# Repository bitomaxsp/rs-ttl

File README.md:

# RS232 to TTL converter

Can be used to connect any 5V logic device to RS232 device such as PC

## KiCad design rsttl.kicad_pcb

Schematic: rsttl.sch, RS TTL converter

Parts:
C1: 0.33uF; C_1210_3225Metric_Pad1.42x2.65mm_HandSolder
C2, C4, C5, C6, C7: 1uF; C_0805_2012Metric_Pad1.15x1.40mm_HandSolder
C3: 0.1uF; C_1210_3225Metric_Pad1.42x2.65mm_HandSolder
D1, D2: LED_Small; LED_0805_2012Metric
J1: DB9_Male; DSUB-9_Male_Horizontal_P2.77x2.84mm_EdgePinOffset9.90mm_Hou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
J2: 7-20V Ext; PinHeader_1x02_P2.54mm_Vertical
J3: TTL Data, 5V; PinHeader_1x06_P2.54mm_Vertical
J5: DB9_Female; DSUB-9_Female_Horizontal_P2.77x2.84mm_EdgePinOffset9.90mm_H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
R1, R2: 1k; R_0805_2012Metric_Pad1.15x1.40mm_HandSolder
U1: NCP1117; SOT-223-3_TabPin2
U2: MAX232; SOP-16_4.55x10.3mm_P1.27mm

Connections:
+5V: C3.1, C4.1, D1.2 (A), D2.2 (A), J3.2, U1.2, U2.16 (VCC)
GND: C1.2, C3.2, C4.2, C6.2, C7.1, J1.5, J2.1, J3.1, J5.5, U1.1, U2.15 (GND)
unnamed: C2.1, U2.1 (C1+)
unnamed: C2.2, U2.3 (C1-)
unnamed: C5.1, U2.4 (C2+)
unnamed: C5.2, U2.5 (C2-)
unnamed: C6.1, U2.2 (VS+)
unnamed: C7.2, U2.6 (VS-)
unnamed: D1.1 (K), R1.2
unnamed: D2.1 (K), R2.2
unnamed: J1.2, J3.3, R2.1, U2.9 (R2OUT)
unnamed: J1.3, J3.4, R1.1, U2.10 (T2IN)
unnamed: J1.7, J3.5, U2.11 (T1IN)
unnamed: J1.8, J3.6, U2.12 (R1OUT)
unnamed: J5.2, U2.7 (T2OUT)
unnamed: J5.3, U2.8 (R2IN)
unnamed: J5.7, U2.13 (R1IN)
unnamed: J5.8, U2.14 (T1OUT)
VCC: C1.1, J2.2, U1.3

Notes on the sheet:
TTL 5V
RS232-PC
CTS
RTS

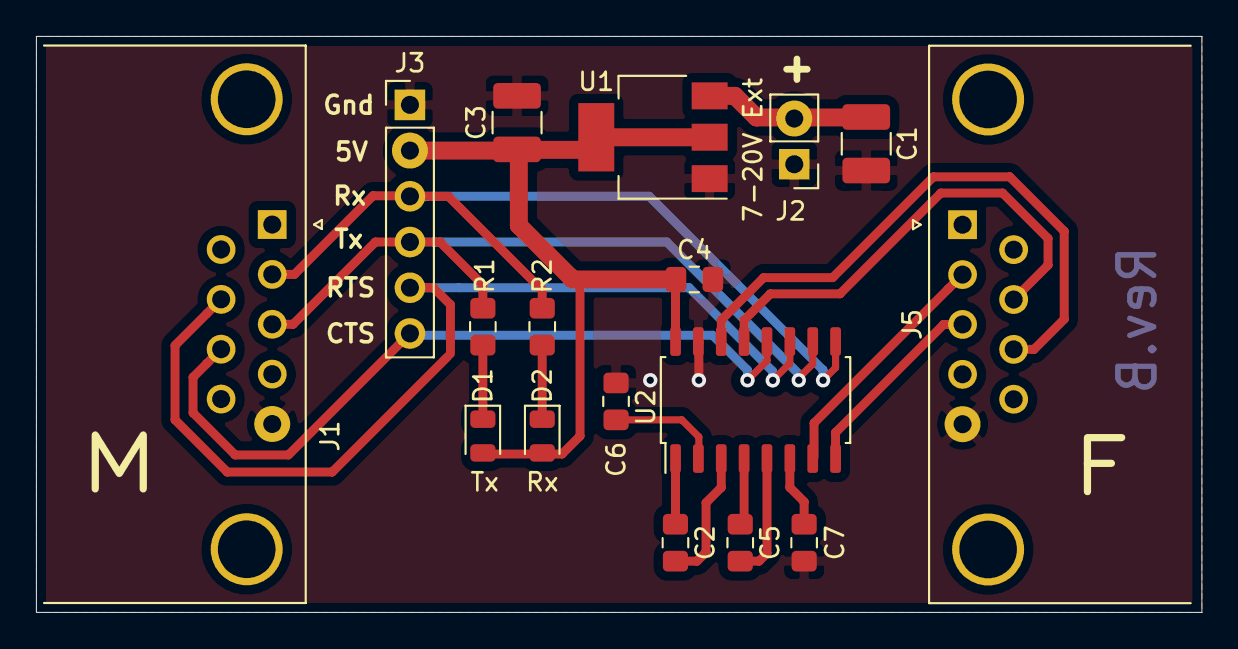
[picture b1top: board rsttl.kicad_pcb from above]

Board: 2 copper layers, 64.8 x 32.0 mm, 17 parts (0 on the bottom side), 19 nets.

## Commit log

2019-10-03 Initial version
2019-10-03 Try new layour
2019-10-04 Add readme
2019-10-04 Remove bak
2019-10-30 Layout revA
2019-10-30 Add symbols
2019-11-08 some improvements
2019-11-12 rm bak
2019-12-13 'Fixes'
2020-01-18 revA to prod
2020-03-12 Rev.B
